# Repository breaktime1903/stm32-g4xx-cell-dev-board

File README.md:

# STM32G4xx Cell DevBoard开发板

一时兴起无聊做的STM32G4开发板（因为G474/G431两个芯片pin2pin兼容所以在上面加了个丝印区分，应该是通用的吧），称之为Cell是因为这玩意确实比较小巧，目前功能如下：

- 25MHz HSE晶振，32.768KHz LSE晶振
- USB Type-C接口（占用PA11，PA12）
- 0.91寸SSD1306 128x32 OLED显示屏，OLED使用PB8（SCL），PB9（SDA）作为引脚，而PB8与BOOT0复用，使用前需要在STM32CubeProgrammer修改Option Bytes
- TPS54302降压供电，最高支持28V输入电压，最大电流为2A（受制于电感

后面应该会基于这个板子设计底板。

### 目前已经打样验证，可放心使用

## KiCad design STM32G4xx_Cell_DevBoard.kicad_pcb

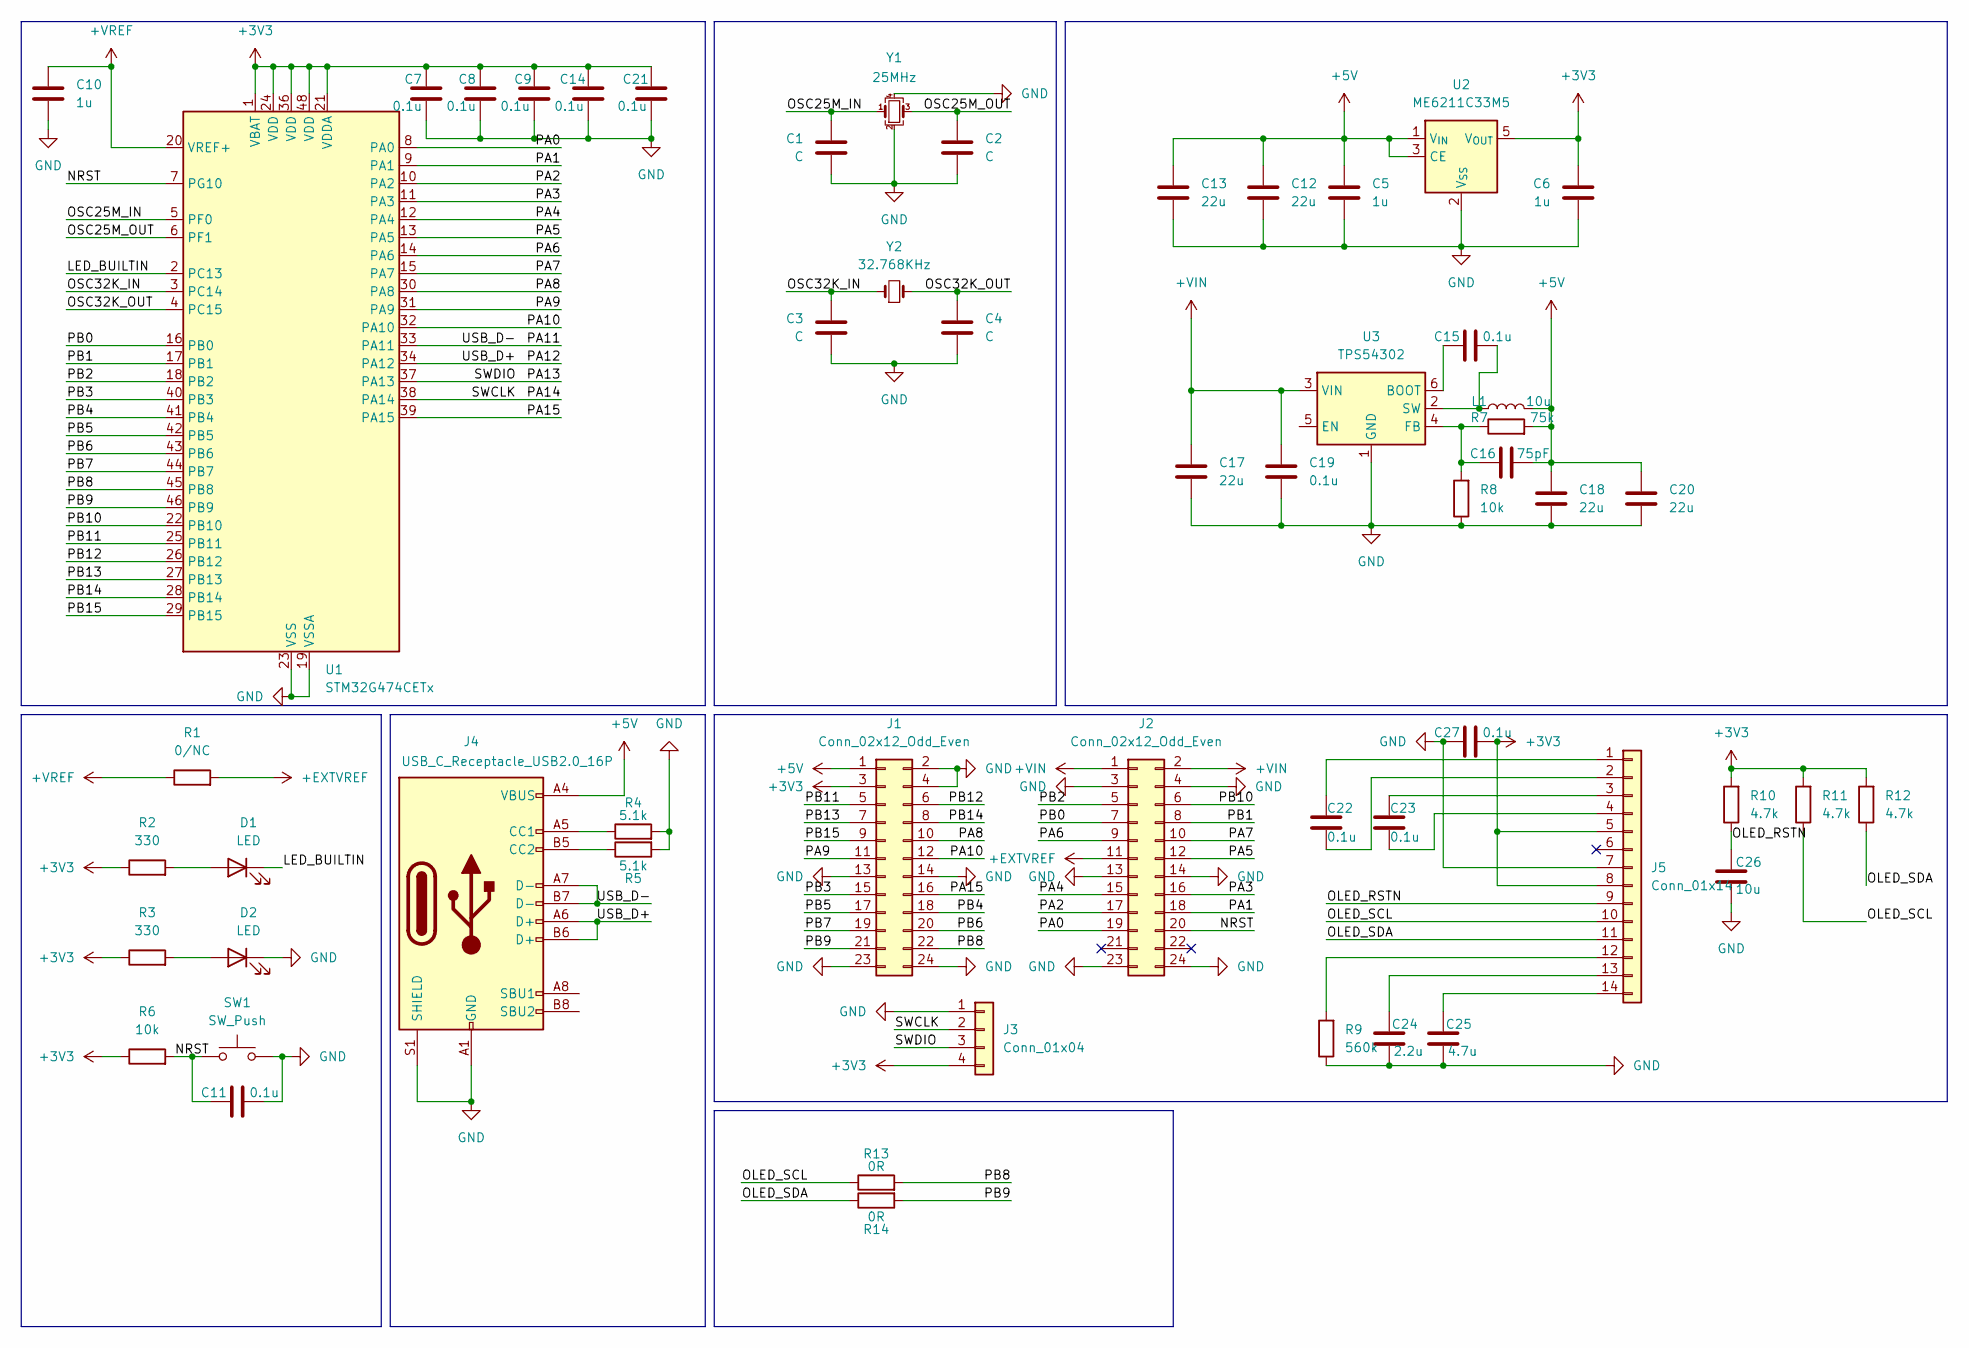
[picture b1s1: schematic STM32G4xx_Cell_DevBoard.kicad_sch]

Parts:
C1, C2, C3, C4: C; C_0603_1608Metric
C5, C6, C10: 1u; C_0603_1608Metric
C7, C8, C9, C11, C14, C15, C19, C21, C22, C23, C27: 0.1u; C_0603_1608Metric
C12, C13, C17, C18, C20: 22u; C_1206_3216Metric
C16: 75pF; C_0603_1608Metric
C24: 2.2u; C_0603_1608Metric
C25: 4.7u; C_0603_1608Metric
C26: 10u; C_0603_1608Metric
D1, D2: LED; LED_0603_1608Metric
J1, J2: Conn_02x12_Odd_Even; PinHeader_2x12_P2.54mm_Vertical
J3: Conn_01x04; PinHeader_1x04_P2.54mm_Horizontal
J4: USB_C_Receptacle_USB2.0_16P; USB_C_Receptacle_XKB_U262-16XN-4BVC11
J5: Conn_01x14; OLED-SMD_14P-P0.62
L1: 10u; L_Changjiang_FXL0530
R1: 0/NC; R_0603_1608Metric
R2, R3: 330; R_0603_1608Metric
R4, R5: 5.1k; R_0603_1608Metric
R6, R8: 10k; R_0603_1608Metric
R7: 75k; R_0603_1608Metric
R9: 560k; R_0603_1608Metric
R10, R11, R12: 4.7k; R_0603_1608Metric
R13, R14: 0R; R_0603_1608Metric
SW1: SW_Push; 3_4微动开关
U1: STM32G474CETx; LQFP-48_7x7mm_P0.5mm
U2: ME6211C33M5; SOT-23-5
U3: TPS54302; SOT-23-6
Y1: 25MHz; Crystal_SMD_3225-4Pin_3.2x2.5mm
Y2: 32.768KHz; Crystal_SMD_3215-2Pin_3.2x1.5mm

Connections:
+3V3: C6.1, C7.1, C8.1, C9.1, C14.1, C21.1, C27.2, J1.3, J3.4, J5.5, J5.8, R2.1, R3.1, R6.1, R10.2, R11.2, R12.2, U1.1 (VBAT), U1.21 (VDDA), U1.24 (VDD), U1.36 (VDD), U1.48 (VDD), U2.5 (V_{OUT})
+5V: C5.1, C12.1, C13.1, C16.2, C18.1, C20.1, J1.1, J4.A4 (VBUS), J4.A9 (VBUS), J4.B4 (VBUS), J4.B9 (VBUS), L1.2, R7.2, U2.1 (V_{IN}), U2.3 (CE)
+EXTVREF: J2.11, R1.2
+VIN: C17.1, C19.1, J2.1, J2.2, U3.3 (VIN)
+VREF: C10.1, R1.1, U1.20 (VREF+)
/LED_BUILTIN: D1.1 (K), U1.2 (PC13)
/NRST: C11.1, J2.20, R6.2, SW1.1, U1.7 (PG10)
/OLED_RSTN: C26.1, J5.9, R10.1
/OLED_SCL: J5.10, R11.1, R13.1
/OLED_SDA: J5.11, R12.1, R14.1
/OSC25M_IN: C1.1, U1.5 (PF0), Y1.1
/OSC25M_OUT: C2.1, U1.6 (PF1), Y1.3
/OSC32K_IN: C3.1, U1.3 (PC14), Y2.1
/OSC32K_OUT: C4.1, U1.4 (PC15), Y2.2
/PA0: J2.19, U1.8 (PA0)
/PA1: J2.18, U1.9 (PA1)
/PA2: J2.17, U1.10 (PA2)
/PA3: J2.16, U1.11 (PA3)
/PA4: J2.15, U1.12 (PA4)
/PA5: J2.12, U1.13 (PA5)
/PA6: J2.9, U1.14 (PA6)
/PA7: J2.10, U1.15 (PA7)
/PA8: J1.10, U1.30 (PA8)
/PA9: J1.11, U1.31 (PA9)
/PA10: J1.12, U1.32 (PA10)
/PA11: J4.A7 (D-), J4.B7 (D-), U1.33 (PA11)
/PA12: J4.A6 (D+), J4.B6 (D+), U1.34 (PA12)
/PA13: J3.3, U1.37 (PA13)
/PA14: J3.2, U1.38 (PA14)
/PA15: J1.16, U1.39 (PA15)
/PB0: J2.7, U1.16 (PB0)
/PB1: J2.8, U1.17 (PB1)
/PB2: J2.5, U1.18 (PB2)
/PB3: J1.15, U1.40 (PB3)
/PB4: J1.18, U1.41 (PB4)
/PB5: J1.17, U1.42 (PB5)
/PB6: J1.20, U1.43 (PB6)
/PB7: J1.19, U1.44 (PB7)
/PB8: J1.22, R13.2, U1.45 (PB8)
/PB9: J1.21, R14.2, U1.46 (PB9)
/PB10: J2.6, U1.22 (PB10)
/PB11: J1.5, U1.25 (PB11)
/PB12: J1.6, U1.26 (PB12)
/PB13: J1.7, U1.27 (PB13)
/PB14: J1.8, U1.28 (PB14)
/PB15: J1.9, U1.29 (PB15)
GND: C1.2, C2.2, C3.2, C4.2, C5.2, C6.2, C7.2, C8.2, C9.2, C10.2, C11.2, C12.2, C13.2, C14.2, C17.2, C18.2, C19.2, C20.2, C21.2, C24.2, C25.2, C26.2, C27.1, D2.1 (K), J1.2, J1.4, J1.13, J1.14, J1.23, J1.24, J2.3, J2.4, J2.13, J2.14, J2.23, J2.24, J3.1, J4.A1 (GND), J4.A12 (GND), J4.B1 (GND), J4.B12 (GND), J4.S1 (SHIELD), J5.7, R4.2, R5.2, R8.1, R9.1, SW1.2, U1.19 (VSSA), U1.23 (VSS), U1.35 (VSS), U1.47 (VSS), U2.2 (V_{SS}), U3.1 (GND), Y1.2, Y1.4
unnamed: D1.2 (A), R2.2
unnamed: D2.2 (A), R3.2
unnamed: J4.A5 (CC1), R4.1
unnamed: J4.B5 (CC2), R5.1
unnamed: C22.1, J5.1
unnamed: C22.2, J5.2
unnamed: C23.1, J5.3
unnamed: C23.2, J5.4
unnamed: J5.12, R9.2
unnamed: C24.1, J5.13
unnamed: C25.1, J5.14
unnamed: C15.1, U3.6 (BOOT)
unnamed: C16.1, R7.1, R8.2, U3.4 (FB)
unnamed: C15.2, L1.1, U3.2 (SW)

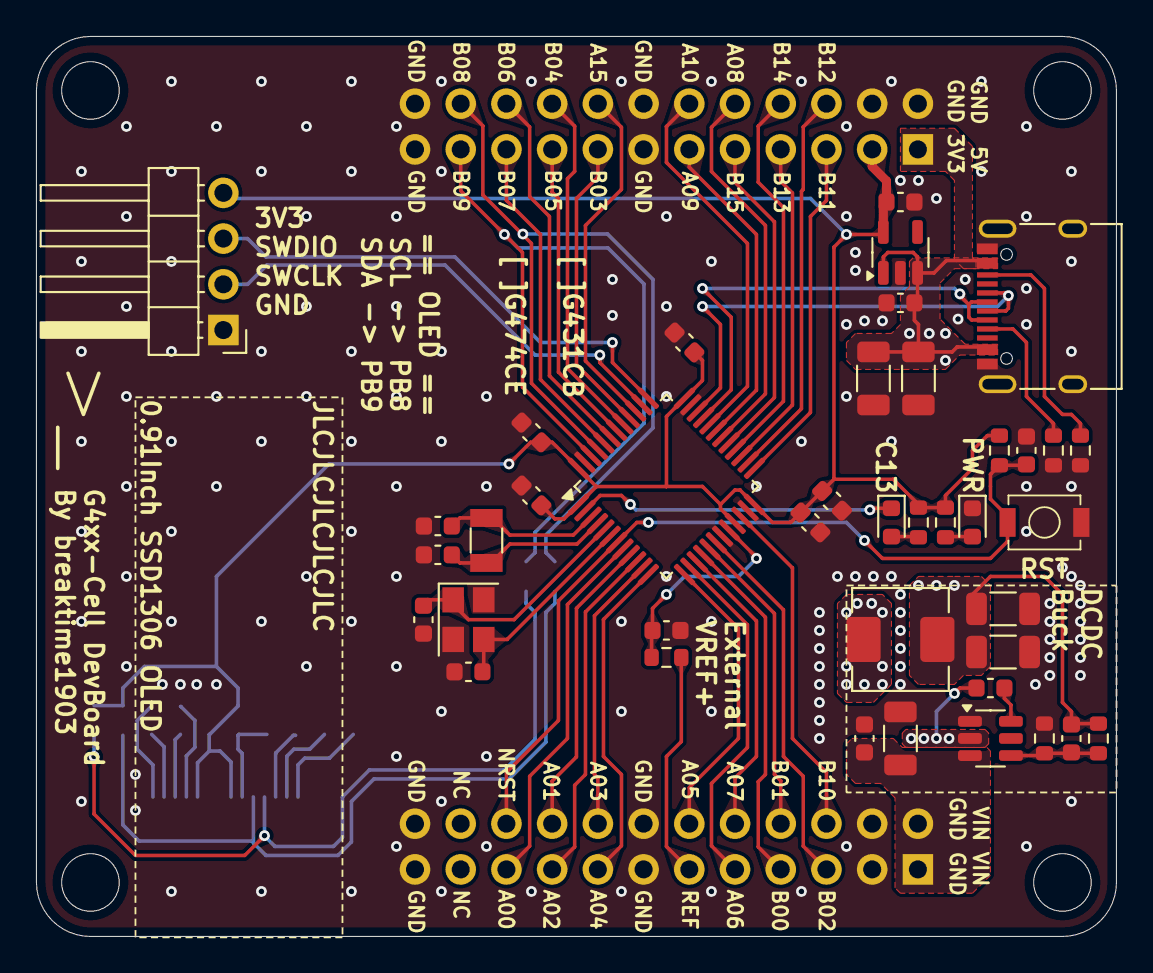
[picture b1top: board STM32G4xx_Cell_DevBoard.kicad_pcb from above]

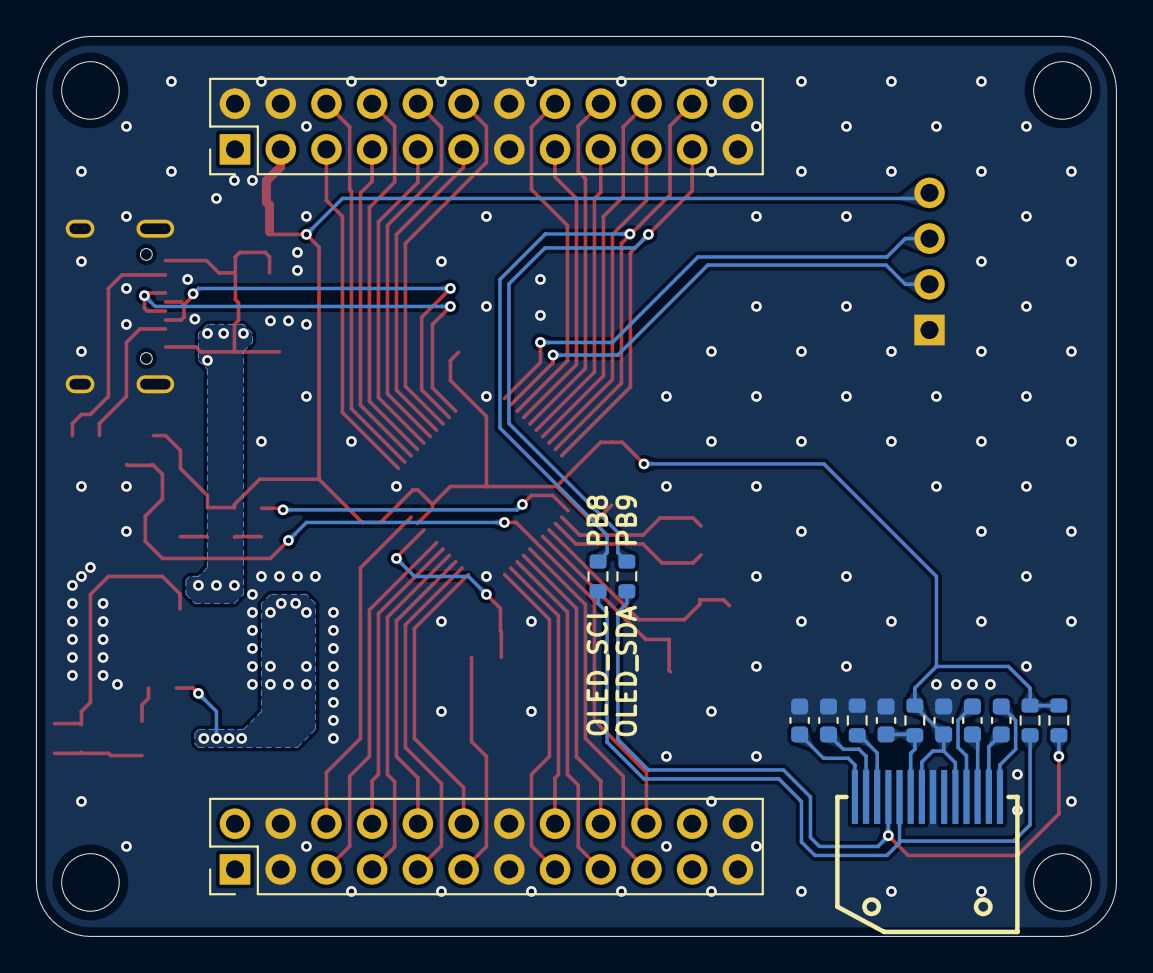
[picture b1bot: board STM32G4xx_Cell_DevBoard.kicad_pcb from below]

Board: 2 copper layers, 60.0 x 50.0 mm, 55 parts (15 on the bottom side), 61 nets.

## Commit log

2025-05-09 上传文件
2025-05-09 Create LICENSE
    添加LICENSE
2025-05-09 删除重复的工程文件
2025-05-11 添加库文件并修改
2025-05-11 添加自己的库文件（之前忘记添加了）
